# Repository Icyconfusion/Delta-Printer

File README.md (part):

# Delta Printer
An STM32 based delta style 3D printer running Marlin firmware. The printer features a custom PCB motherboard, LCD, and 220mm diameter x roughly 200mm build volume. I designed this project to expand on my understanding of 3D printer hardware and mechanics through non-standard motion.

**Note to reviewer:** My JLCPCB/MC screenshot is inclusive of tax and cheapest shipping option, it went into my "orders" tab despite not being paid for, but that is the total price, and the checkout page. Thank you:)

## Assembly
The key assembly ofthe printer is a triangular prism made of 2020 T slot aluminium profiles. Using 3d printed brackets, shorter T slots of lengths 340mm for the top and 290 for the bottom are arranged into triangles. 500mm T slot join these triangles. Two profiles are used for each tower to increase stiffness. The bottom bracket extends the height of the printer without needing extra T slot. Brackets are mounted using T nuts.

400mm MGN12H linear rails are mounted to the inside profile of each tower using M3x8 screws.

To mount the NEMA17 stepper motors, the motors are screwed into the mount bracket, which attaches to the inside of the two bottom triangles.

Bottom covers are added and the PCB is placed in the groove in the centre.

Idle pulleys are mounted to the top bracket with an M5 screw. The carriages are assembled with the ball joints screwed onto the carriage. M3 screws are threaded into the heat inserts and the GT2 belt is mounted. The carbon tube has an M3 stud glue into each end, which is threaded into the ball joint on each end.

### Effector Assembly
To assemble the effector, first mount the NEMA 17 stepper and filament gear.

Then mount the CR6-SE hotend into the heat inserts.

4010 fans mount on the back and side where they are ducted to the nozzle/part.

The extruder arm provides tension to the filament gear to ensure accurate and reliable extrusion of filament. The arm is spring loaded to push an 11x5x5 bearing, squeezing the filament against the drive gear. The arm pivots around the top left M3 NEMA 17 mounting screw. An M5 screw above this is threaded into the effector knob, and a spring in this spot provides tension. Finally, the ball joints are attached, and can be connected to the arms on the carriages.

To start closing the base compartment and installing the bed, the LCD must be installed. The LCD is screwed through the back into heat inserts in the LCD module printed part. This module is then mounted onto LCD base covers using heat inserts. This is then mounted onto the base using T nuts.

Base covers are mounted onto one of the other sides.

The third side holds the PSU. The PSU is held in its compartment, which is mounted to the frame in place. A base cover is mounted next to it. There is a hole in the base cover next to it for power cables to run from to PSU to the wall outlet.

Now the bed can be installed. To do this, printed bed supports are installed on the base. The bed then screws into these. If needed, depending on exact specifications of the bed, the holes to mount the bed can be made larger by printing or drilling.

To mount limit switches, the switches are screwed into heat inserts in the bracket, then mounted to the bottom of the towers. After this the printer is assembled.

## Electronics
The printer features a 2 layer PCB motherboard I designed around an STM32F407VGT6. TMC2209 drivers are used to control stepper motors, and subsequently motion. The board utilises mostly SMD components to minimise space and layer requirements. Power is brought onto the board using 7.62mm pitch screw terminals, which connect to the 24V 600w PSU. A buck converter and linear regulator convert this down to 5V and 3.3V logic levels. 5V is used only for the buck converter and the EXP1 header for the LCD. The LCD used it a BTT Mini 12864 V2.0, which interfaces with the PCB via EXP1 and EXP2 headers. The LCD also has an encoder, button and SD card reader. The heaters (hotend and bed if required in future) are controlled through TO-252-3 AOD4184 MOSFETs. Lower power mosfets, SOT-23 AO3400 MOSFETs, are used to control the 24V fans. There is a USB-C receptacle for firmware flashing, and an SWD header if needed. Most resistors and capacitors are size 0805, though there are exceptionswhere required. Because I am using the STM32, no external flash is required, as it is onboard.

Driver hierarchical sheet:

MOSFET hierarchical sheet:

Power:

EXP1 and EXP2:

The PCB is organised with drivers up the top. Power on the left edge, with the buck converter, regulator, power input terminal and fuse. MOSFETs are on the bottom, heaters on the right hand side. On the right edge, there is the USB-C receptacle, thermistors, endstops and LCD headers. The STM32 is situated in the center.

## Firmware
The firmware used is Marlin firmware. The firmware has been configured to match a delta printer with delta kinematics. Additionally, it has been configured for my custom motherboard by creating a unique pin mapping for the printer. The config and pin map files are in the firmware folder of the repo, along with the complete marlin .zip build folder.

## BOM
### Printed Parts

|Part| Quantity| Image|
|---|---|---|
|Bottom bracket | 3 |  |
|Top bracket | 3 |  |
|Bottom cover | 3 |  |
|Bed support | 3 |  |
|Motor mount | 3 |  |
|Carriage | 3 |  |
|PSU compartment | 3 |  |
|Base cover LCD | 2 |  |
|Base cover | 2 |  |
|Base cover PSU | 1 |  |
|LCD front cover | 1 |  |
|Extruder | 1 |  |
|Drive arm | 1 |  |
|Limit switch bracket | 3 |  |

### Parts already owned
| Part | Quantity | Description |
|--|--|--|
|T slot | 6 | 500mm 2020 T slot profiles |
|Linear rail | 3 | MGN12H 400mm linear rail and carriage |
|Motor | 4 | NEMA 17 stepper motor |
| Hotend | 1 | CR6 SE hotend |
| Fan | 2 | 4010 24v blower fan |
| GT2 bearing | 3 | 5mm bore gt2 idler bearing |
| GT2 gear | 3 | GT2 20T gear |
|LCD | 1 | BTT mini 12864 V2.0 LCD |
| Limit switch | 3 | Standard limit switch |
| T nut | - | M5 and M3 T nuts |
| PSU | 1 | 24V 600w PSU |

### Purchased parts
|Product            |Quantity|Description                                                                                                                  |Total cost (USD)|Supplier  |Link                                                                                                                                                                                                                                                                                                                                                                                                                                                                                                                                                                                                                                                                                                                                                                                                                        |
|-------------------|--------|-----------------------------------------------------------------------------------------------------------------------------|----------------|----------|----------------------------------------------------------------------------------------------------------------------------------------------------------------------------------------------------------------------------------------------------------------------------------------------------------------------------------------------------------------------------------------------------------------------------------------------------------------------------------------------------------------------------------------------------------------------------------------------------------------------------------------------------------------------------------------------------------------------------------------------------------------------------------------------------------------------------|
|100nF Capacitors   |26      |100nF 0805 ceramic capacitors for PCB                                                                                        |2.31            |Aliexpress|https://www.aliexpress.com/item/1005011894977575.html?spm=a2g0o.productlist.main.41.69b475e66t3VJX&algo_pvid=395ae593-2082-45a5-ad42-2ee72ec24400&algo_exp_id=395ae593-2082-45a5-ad42-2ee72ec24400-38&pdp_ext_f=%7B%22order%22%3A%2264%22%2C%22eval%22%3A%221%22%2C%22fromPage%22%3A%22search%22%7D&pdp_npi=6%40dis%21AUD%210.98%210.74%21%21%210.69%210.52%21%402101e2b017803787116784136eb256%2112000056926137114%21sea%21AU%210%21ABX%211%210%21n_tag%3A-29910%3Bd%3A6fbdfe4b%3Bm03_new_user%3A-29895&curPageLogUid=lO0BHaX0NqCM&utparam-url=scene%3Asearch%7Cquery_from%3A%7Cx_object_id%3A1005011894977575%7C_p_origin_prod%3A                                                                                                                                                                                         |
|100uF - Low ESR Cap|6       |50V 100uF Low ESR caps in 6.3x7.7 package. Used for Vm on TMC2209                                                            |3.69            |Aliexpress|https://www.aliexpress.com/item/1005006846973435.html                                                                                                                                                                                                                                                                                                                                                                                                                                                                                                                                                                                                                                                                                                                                                                       |
|2.2uF cap          |6       |0805 2.2uF 50V ceramic capacitors                                                                                            |2.2             |Aliexpress|https://www.aliexpress.com/item/1005007293718666.html?spm=a2g0o.productlist.main.8.67be145epeTiPJ&algo_pvid=53e6a399-9eba-48a6-b5d2-d96bd9cce18e&aem_p4p_detail=20260601225849174814213877420004833943&algo_exp_id=53e6a399-9eba-48a6-b5d2-d96bd9cce18e-7&pdp_ext_f=%7B%22order%22%3A%221222%22%2C%22spu_best_type%22%3A%22price%22%2C%22eval%22%3A%221%22%2C%22fromPage%22%3A%22search%22%7D&pdp_npi=6%40dis%21AUD%212.85%212.85%21%21%2113.59%2113.59%21%402103128917803799289523918ea094%2112000040093563143%21sea%21AU%210%21ABX%211%210%21n_tag%3A-29910%3Bd%3A6fbdfe4b%3Bm03_new_user%3A-29895&curPageLogUid=OS4dkcks5GAl&utparam-url=scene%3Asearch%7Cquery_from%3A%7Cx_object_id%3A1005007293718666%7C_p_origin_prod%3A&search_p4p_id=20260601225849174814213877420004833943_2                                      |
|22nF cap           |4       |0805 22nF 50V ca-                                                                                                            |2.2             |Aliexpress|https://www.aliexpress.com/item/1005011894977575.html?spm=a2g0o.productlist.main.41.69b475e66t3VJX&algo_pvid=395ae593-2082-45a5-ad42-2ee72ec24400&algo_exp_id=395ae593-2082-45a5-ad42-2ee72ec24400-38&pdp_ext_f=%7B%22order%22%3A%2264%22%2C%22eval%22%3A%221%22%2C%22fromPage%22%3A%22search%22%7D&pdp_npi=6%40dis%21AUD%210.98%210.74%21%21%210.69%210.52%21%402101e2b017803787116784136eb256%2112000056926137114%21sea%21AU%210%21ABX%211%210%21n_tag%3A-29910%3Bd%3A6fbdfe4b%3Bm03_new_user%3A-29895&curPageLogUid=lO0BHaX0NqCM&utparam-url=scene%3Asearch%7Cquery_from%3A%7Cx_object_id%3A1005011894977575%7C_p_origin_prod%3A                                                                                                                                                                                         |
|1uF cap            |4       |0805 1uF 50V capacitor                                                                                                       |2.04            |Aliexpress|https://www.aliexpress.com/item/1005007293718666.html?spm=a2g0o.productlist.main.8.67be145epeTiPJ&algo_pvid=53e6a399-9eba-48a6-b5d2-d96bd9cce18e&aem_p4p_detail=20260601225849174814213877420004833943&algo_exp_id=53e6a399-9eba-48a6-b5d2-d96bd9cce18e-7&pdp_ext_f=%7B%22order%22%3A%221222%22%2C%22spu_best_type%22%3A%22price%22%2C%22eval%22%3A%221%22%2C%22fromPage%22%3A%22search%22%7D&pdp_npi=6%40dis%21AUD%212.85%212.85%21%21%2113.59%2113.59%21%402103128917803799289523918ea094%2112000040093563143%21sea%21AU%210%21ABX%211%210%21n_tag%3A-29910%3Bd%3A6fbdfe4b%3Bm03_new_user%3A-29895&curPageLogUid=OS4dkcks5GAl&utparam-url=scene%3Asearch%7Cquery_from%3A%7Cx_object_id%3A1005007293718666%7C_p_origin_prod%3A&search_p4p_id=20260601225849174814213877420004833943_2                                      |
|18pF cap           |2       |0805 18pF cap for crystal                                                                                                    |2.52            |Aliexpress|https://www.aliexpress.com/item/1005002958706092.html?spm=a2g0o.productlist.main.1.3511QjeLQjeLPI&algo_pvid=3a26b9ba-d000-4d83-9a75-3d450696f550&algo_exp_id=3a26b9ba-d000-4d83-9a75-3d450696f550-0&pdp_ext_f=%7B%22order%22%3A%22135%22%2C%22eval%22%3A%221%22%2C%22fromPage%22%3A%22search%22%7D&pdp_npi=6%40dis%21AUD%211.79%211.79%21%21%211.26%211.26%21%4021030a4b17807228650825953eb029%2112000022968072311%21sea%21AU%217099856219%21ABX%211%210%21n_tag%3A-29910%3Bd%3A6fbdfe4b%3Bm03_new_user%3A-29895&curPageLogUid=HO0lalvIulA4&utparam-url=scene%3Asearch%7Cquery_from%3A%7Cx_object_id%3A1005002958706092%7C_p_origin_prod%3A                                                                                                                                                                                 |
|22uF cap           |4       |0805 22uF 50V capacitor                                                                                                      |2.86            |Aliexpress|https://www.aliexpress.com/item/1005007293718666.html?spm=a2g0o.productlist.main.8.67be145epeTiPJ&algo_pvid=53e6a399-9eba-48a6-b5d2-d96bd9cce18e&aem_p4p_detail=20260601225849174814213877420004833943&algo_exp_id=53e6a399-9eba-48a6-b5d2-d96bd9cce18e-7&pdp_ext_f=%7B%22order%22%3A%221222%22%2C%22spu_best_type%22%3A%22price%22%2C%22eval%22%3A%221%22%2C%22fromPage%22%3A%22search%22%7D&pdp_npi=6%40dis%21AUD%212.85%212.85%21%21%2113.59%2113.59%21%402103128917803799289523918ea094%2112000040093563143%21sea%21AU%210%21ABX%211%210%21n_tag%3A-29910%3Bd%3A6fbdfe4b%3Bm03_new_user%3A-29895&curPageLogUid=OS4dkcks5GAl&utparam-url=scene%3Asearch%7Cquery_from%3A%7Cx_object_id%3A1005007293718666%7C_p_origin_prod%3A&search_p4p_id=20260601225849174814213877420004833943_2                                      |
|10uF cap           |6       |0805 10uF cap                                                                                                                |2.54            |Aliexpress|https://www.aliexpress.com/item/1005007293718666.html?spm=a2g0o.productlist.main.8.67be145epeTiPJ&algo_pvid=53e6a399-9eba-48a6-b5d2-d96bd9cce18e&aem_p4p_detail=20260601225849174814213877420004833943&algo_exp_id=53e6a399-9eba-48a6-b5d2-d96bd9cce18e-7&pdp_ext_f=%7B%22order%22%3A%221222%22%2C%22spu_best_type%22%3A%22price%22%2C%22eval%22%3A%221%22%2C%22fromPage%22%3A%22search%22%7D&pdp_npi=6%40dis%21AUD%212.85%212.85%21%21%2113.59%2113.59%21%402103128917803799289523918ea094%2112000040093563143%21sea%21AU%210%21ABX%211%210%21n_tag%3A-29910%3Bd%3A6fbdfe4b%3Bm03_new_user%3A-29895&curPageLogUid=OS4dkcks5GAl&utparam-url=scene%3Asearch%7Cquery_from%3A%7Cx_object_id%3A1005007293718666%7C_p_origin_prod%3A&search_p4p_id=20260601225849174814213877420004833943_2                                      |
|220pF cap          |1       |0805 220pF 50V cap                                                                                                           |4.04            |Aliexpress|https://www.aliexpress.com/item/1005011884524334.html?spm=a2g0o.productlist.main.8.50ab6ab5yWojEX&algo_pvid=5edf1c78-ef25-4421-bfb1-3e1d6e4784bc&algo_exp_id=5edf1c78-ef25-4421-bfb1-3e1d6e4784bc-7&pdp_ext_f=%7B%22order%22%3A%2235%22%2C%22eval%22%3A%221%22%2C%22fromPage%22%3A%22search%22%7D&pdp_npi=6%40dis%21AUD%213.81%211.79%21%21%2118.11%218.51%21%40210328d417806369446965838ef751%2112000056880413140%21sea%21AU%210%21ABX%211%210%21n_tag%3A-29910%3Bd%3A6fbdfe4b%3Bm03_new_user%3A-29895&curPageLogUid=1xTiDLuHV5Su&utparam-url=scene%3Asearch%7Cquery_from%3A%7Cx_object_id%3A1005011884524334%7C_p_origin_prod%3A                                                                                                                                                                                          |
|SS34 diode         |1       |SS34 SMA Schottky diode                                                                                                      |2.89            |Aliexpress|https://www.aliexpress.com/item/1005003929814084.html?spm=a2g0o.productlist.main.1.7ba564e91Bl9Po&algo_pvid=39ff2f7f-65b5-4324-9e76-e1229462bde4&algo_exp_id=39ff2f7f-65b5-4324-9e76-e1229462bde4-0&pdp_ext_f=%7B%22order%22%3A%22312%22%2C%22eval%22%3A%221%22%2C%22fromPage%22%3A%22search%22%7D&pdp_npi=6%40dis%21AUD%213.94%211.41%21%21%212.76%210.98%21%402101ef5e17806371422707336ed5cd%2112000027492300397%21sea%21AU%210%21ABX%211%210%21n_tag%3A-29910%3Bd%3A6fbdfe4b%3Bm03_new_user%3A-29895%3BpisId%3A5000000204867275&curPageLogUid=NnPur3r1YfyF&utparam-url=scene%3Asearch%7Cquery_from%3A%7Cx_object_id%3A1005003929814084%7C_p_origin_prod%3A                                                                                                                                                               |
|Ferrite bead       |1       |0805 600R 100mhz ferrite bead                                                                                                |3.93            |Aliexpress|https://www.aliexpress.com/item/1005003127666910.html?spm=a2g0o.productlist.main.37.ba11ISfCISfCeO&algo_pvid=b19fe644-ee9e-45ce-8c38-43ce983eb4d3&algo_exp_id=b19fe644-ee9e-45ce-8c38-43ce983eb4d3-34&pdp_ext_f=%7B%22order%22%3A%2225%22%2C%22eval%22%3A%221%22%2C%22fromPage%22%3A%22search%22%7D&pdp_npi=6%40dis%21AUD%215.52%214.72%21%21%213.87%213.31%21%40210337c117807205436898267e16f1%2112000024246365910%21sea%21AU%217099856219%21ABX%211%210%21n_tag%3A-29910%3Bd%3A6fbdfe4b%3Bm03_new_user%3A-29895&curPageLogUid=ES5AkXMpY2mV&utparam-url=scene%3Asearch%7Cquery_from%3A%7Cx_object_id%3A1005003127666910%7C_p_origin_prod%3A                                                                                                                                                                                |
|IDC header         |2       |2x5 pin 2.54mm IDC header for EXP1/2                                                                                         |4.77            |Aliexpress|https://www.aliexpress.com/item/32658384492.html?spm=a2g0o.productlist.main.1.219e2670Eo0Se8&algo_pvid=fe8eff41-56a5-4592-8ccd-295c5888be36&algo_exp_id=fe8eff41-56a5-4592-8ccd-295c5888be36-0&pdp_ext_f=%7B%22order%22%3A%22191%22%2C%22eval%22%3A%221%22%2C%22fromPage%22%3A%22search%22%7D&pdp_npi=6%40dis%21AUD%213.22%211.15%21%21%212.26%210.81%21%402101eecd17806372074926845e0b1c%2159817550672%21sea%21AU%210%21ABX%211%210%21n_tag%3A-29910%3Bd%3A6fbdfe4b%3Bm03_new_user%3A-29895&curPageLogUid=g4IB6NhYXd4C&utparam-url=scene%3Asearch%7Cquery_from%3A%7Cx_object_id%3A32658384492%7C_p_origin_prod%3A                                                                                                                                                                                                          |
|JST-XH header      |7       |JST-XH 2.54mm header for conencting heaters and fans                                                                         |1.83            |Aliexpress|https://www.aliexpress.com/item/1005004985397880.html?spm=a2g0o.productlist.main.23.40e65899Of5PUE&algo_pvid=1977cbec-ffa5-4de8-831c-9440196d8bf1&algo_exp_id=1977cbec-ffa5-4de8-831c-9440196d8bf1-22&pdp_ext_f=%7B%22order%22%3A%222875%22%2C%22eval%22%3A%221%22%2C%22fromPage%22%3A%22search%22%7D&pdp_npi=6%40dis%21AUD%211.97%211.41%21%21%211.38%210.99%21%402101e2b417806373261363795eedd2%2112000031243962104%21sea%21AU%210%21ABX%211%210%21n_tag%3A-29910%3Bd%3A6fbdfe4b%3Bm03_new_user%3A-29895%3BpisId%3A5000000204867275&curPageLogUid=7n7ud5jLy3vZ&utparam-url=scene%3Asearch%7Cquery_from%3A%7Cx_object_id%3A1005004985397880%7C_p_origin_prod%3A                                                                                                                                                            |
|10uH inductor      |1       |6x6x3 10uH inductor                                                                                                          |3.5             |Aliexpress|https://www.aliexpress.com/item/1005006817003873.html?spm=a2g0o.productlist.main.6.307049c0TMTVHT&algo_pvid=e79df2b3-a062-49aa-af8c-c6f5cb47ec49&algo_exp_id=e79df2b3-a062-49aa-af8c-c6f5cb47ec49-5&pdp_ext_f=%7B%22order%22%3A%22163%22%2C%22eval%22%3A%221%22%2C%22fromPage%22%3A%22search%22%7D&pdp_npi=6%40dis%21AUD%214.18%213.83%21%21%2119.87%2118.21%21%402103274e17807207366446547eda14%2112000038400661794%21sea%21AU%217099856219%21ABX%211%210%21n_tag%3A-29910%3Bd%3A6fbdfe4b%3Bm03_new_user%3A-29895&curPageLogUid=Uw0smIdCVuNn&utparam-url=scene%3Asearch%7Cquery_from%3A%7Cx_object_id%3A1005006817003873%7C_p_origin_prod%3A                                                                                                                                                                               |
|MOSFET             |2       |TO252-3 AOD4184 SMD MOSFET for heaters                                                                                       |3.7             |Aliexpress|https://www.aliexpress.com/item/1005006044488568.html?spm=a2g0o.productlist.main.11.4d4c3b5bR8SclD&algo_pvid=a61fbf26-45db-4a52-9034-cc3dcb697579&algo_exp_id=a61fbf26-45db-4a52-9034-cc3dcb697579-10&pdp_ext_f=%7B%22order%22%3A%2295%22%2C%22eval%22%3A%221%22%2C%22fromPage%22%3A%22search%22%7D&pdp_npi=6%40dis%21AUD%215.19%215.19%21%21%213.64%213.64%21%402101d6fe17807216896738122e0f1a%2112000035465188545%21sea%21AU%217099856219%21ABX%211%210%21n_tag%3A-29910%3Bd%3A6fbdfe4b%3Bm03_new_user%3A-29895&curPageLogUid=S5OfV9YlN4WJ&utparam-url=scene%3Asearch%7Cquery_from%3A%7Cx_object_id%3A1005006044488568%7C_p_origin_prod%3A                                                                                                                                                                                |
|Fan MOSFET         |3       |SOT-23 AO3400 SMD MOSFET                                                                                                     |1.87            |Aliexpress|https://www.aliexpress.com/item/1005006286601118.html?spm=a2g0o.productlist.main.9.4ce42ca8iM3y0D&algo_pvid=319f8fc6-8206-46b1-9744-9ac8f71bc98b&algo_exp_id=319f8fc6-8206-46b1-9744-9ac8f71bc98b-8&pdp_ext_f=%7B%22order%22%3A%22371%22%2C%22spu_best_type%22%3A%22price%22%2C%22eval%22%3A%221%22%2C%22fromPage%22%3A%22search%22%7D&pdp_npi=6%40dis%21AUD%212.63%211.41%21%21%2112.49%216.69%21%402101df0e17807218619116715e442e%2112000036629120259%21sea%21AU%217099856219%21ABX%211%210%21n_tag%3A-29910%3Bd%3A6fbdfe4b%3Bm03_new_user%3A-29895%3BpisId%3A5000000204867275&curPageLogUid=dHrfVQrllnN6&utparam-url=scene%3Asearch%7Cquery_from%3A%7Cx_object_id%3A1005006286601118%7C_p_origin_prod%3A                                                                                                                 |
|Resistor 0.5W      |8       |1206 0.5W 0.15 ohm sense resistor for TMC 2209                                                                               |1.62            |Aliexpress|https://www.aliexpress.com/item/1005005905538731.html?spm=a2g0o.productlist.main.22.23a1qQ8UqQ8UMb&algo_pvid=a82ca72a-9188-440a-b602-617bfa6c08b9&algo_exp_id=a82ca72a-9188-440a-b602-617bfa6c08b9-21&pdp_ext_f=%7B%22order%22%3A%2295%22%2C%22eval%22%3A%221%22%2C%22fromPage%22%3A%22search%22%7D&pdp_npi=6%40dis%21AUD%212.28%212.28%21%21%211.60%211.60%21%40210319b717807247218277738eef46%2112000034790583111%21sea%21AU%217099856219%21ABX%211%210%21n_tag%3A-29910%3Bd%3A6fbdfe4b%3Bm03_new_user%3A-29895&curPageLogUid=Pfo42AofQ8rk&utparam-url=scene%3Asearch%7Cquery_from%3A%7Cx_object_id%3A1005005905538731%7C_p_origin_prod%3A                                                                                                                                                                                |
|1K resistor        |5       |0805 1k ohm resistor                                                                                                         |2.48            |Aliexpress|https://www.aliexpress.com/item/32936483115.html?spm=a2g0o.productlist.main.17.1568609eeUmkpk&algo_pvid=3f253524-d59c-408c-95f4-7682587921c2&algo_exp_id=3f253524-d59c-408c-95f4-7682587921c2-16&pdp_ext_f=%7B%22order%22%3A%22226%22%2C%22eval%22%3A%221%22%2C%22fromPage%22%3A%22search%22%7D&pdp_npi=6%40dis%21AUD%213.38%213.38%21%21%212.37%212.37%21%402101df0e17806374475111340ea6b0%2166160253242%21sea%21AU%210%21ABX%211%210%21n_tag%3A-29910%3Bd%3A6fbdfe4b%3Bm03_new_user%3A-29895&curPageLogUid=dNfs5t7vpWyj&utparam-url=scene%3Asearch%7Cquery_from%3A%7Cx_object_id%3A32936483115%7C_p_origin_prod%3A                                                                                                                                                                                                        |
|10k resistor       |12      |0805 10k resistor                                                                                                            |2.53            |Aliexpress|https://www.aliexpress.com/item/32936483115.html?spm=a2g0o.productlist.main.17.1568609eeUmkpk&algo_pvid=3f253524-d59c-408c-95f4-7682587921c2&algo_exp_id=3f253524-d59c-408c-95f4-7682587921c2-16&pdp_ext_f=%7B%22order%22%3A%22226%22%2C%22eval%22%3A%221%22%2C%22fromPage%22%3A%22search%22%7D&pdp_npi=6%40dis%21AUD%213.38%213.38%21%21%212.37%212.37%21%402101df0e17806374475111340ea6b0%2166160253242%21sea%21AU%210%21ABX%211%210%21n_tag%3A-29910%3Bd%3A6fbdfe4b%3Bm03_new_user%3A-29895&curPageLogUid=dNfs5t7vpWyj&utparam-url=scene%3Asearch%7Cquery_from%3A%7Cx_object_id%3A32936483115%7C_p_origin_prod%3A                                                                                                                                                                                                        |
|100 resistor       |6       |100 ohm 0805 resistor                                                                                                        |2.44            |Aliexpress|https://www.aliexpress.com/item/32936483115.html?spm=a2g0o.productlist.main.17.1568609eeUmkpk&algo_pvid=3f253524-d59c-408c-95f4-7682587921c2&algo_exp_id=3f253524-d59c-408c-95f4-7682587921c2-16&pdp_ext_f=%7B%22order%22%3A%22226%22%2C%22eval%22%3A%221%22%2C%22fromPage%22%3A%22search%22%7D&pdp_npi=6%40dis%21AUD%213.38%213.38%21%21%212.37%212.37%21%402101df0e17806374475111340ea6b0%2166160253242%21sea%21AU%210%21ABX%211%210%21n_tag%3A-29910%3Bd%3A6fbdfe4b%3Bm03_new_user%3A-29895&curPageLogUid=dNfs5t7vpWyj&utparam-url=scene%3Asearch%7Cquery_from%3A%7Cx_object_id%3A32936483115%7C_p_origin_prod%3A                                                                                                                                                                                                        |
|5.1K resistor      |2       |0805 5.1k resistor                                                                                                           |2.48            |Aliexpress|https://www.aliexpress.com/item/32936483115.html?spm=a2g0o.productlist.main.17.1568609eeUmkpk&algo_pvid=3f253524-d59c-408c-95f4-7682587921c2&algo_exp_id=3f253524-d59c-408c-95f4-7682587921c2-16&pdp_ext_f=%7B%22order%22%3A%22226%22%2C%22eval%22%3A%221%22%2C%22fromPage%22%3A%22search%22%7D&pdp_npi=6%40dis%21AUD%213.38%213.38%21%21%212.37%212.37%21%402101df0e17806374475111340ea6b0%2166160253242%21sea%21AU%210%21ABX%211%210%21n_tag%3A-29910%3Bd%3A6fbdfe4b%3Bm03_new_user%3A-29895&curPageLogUid=dNfs5t7vpWyj&utparam-url=scene%3Asearch%7Cquery_from%3A%7Cx_object_id%3A32936483115%7C_p_origin_prod%3A                                                                                                                                                                                                        |
|33 resistor        |2       |0805 33 ohm resistor                                                                                                         |2.44            |Aliexpress|https://www.aliexpress.com/item/32936483115.html?spm=a2g0o.productlist.main.17.1568609eeUmkpk&algo_pvid=3f253524-d59c-408c-95f4-7682587921c2&algo_exp_id=3f253524-d59c-408c-95f4-7682587921c2-16&pdp_ext_f=%7B%22order%22%3A%22226%22%2C%22eval%22%3A%221%22%2C%22fromPage%22%3A%22search%22%7D&pdp_npi=6%40dis%21AUD%213.38%213.38%21%21%212.37%212.37%21%402101df0e17806374475111340ea6b0%2166160253242%21sea%21AU%210%21ABX%211%210%21n_tag%3A-29910%3Bd%3A6fbdfe4b%3Bm03_new_user%3A-29895&curPageLogUid=dNfs5t7vpWyj&utparam-url=scene%3Asearch%7Cquery_from%3A%7Cx_object_id%3A32936483115%7C_p_origin_prod%3A                                                                                                                                                                                                        |
|52.3K resistor     |1       |0805 52.3k resistor                                                                                                          |1.8             |Aliexpress|https://www.aliexpress.com/item/1005005184354247.html?spm=a2g0o.productlist.main.1.12dfnIy4nIy4Db&algo_pvid=04236b54-eea0-456f-b46d-5a8e50e54835&algo_exp_id=04236b54-eea0-456f-b46d-5a8e50e54835-0&pdp_ext_f=%7B%22order%22%3A%2275%22%2C%22spu_best_type%22%3A%22price%22%2C%22eval%22%3A%221%22%2C%22fromPage%22%3A%22search%22%7D&pdp_npi=6%40dis%21AUD%212.52%212.52%21%21%2111.99%2111.99%21%402101d6ff17807224801268541e7688%2112000032017603960%21sea%21AU%217099856219%21ABX%211%210%21n_tag%3A-29910%3Bd%3A6fbdfe4b%3Bm03_new_user%3A-29895&curPageLogUid=rQRCWdSXORAa&utparam-url=scene%3Asearch%7Cquery_from%3A%7Cx_object_id%3A1005005184354247%7C_p_origin_prod%3A                                                                                                                                            |
|100k resistor      |1       |0805 100k resistor                                                                                                           |3.04            |Aliexpress|https://www.aliexpress.com/item/1005007183002569.html?spm=a2g0o.productlist.main.1.23aaF519F5192b&algo_pvid=0c0e1b7a-10d1-428c-a6a4-4f6f3e54d974&algo_exp_id=0c0e1b7a-10d1-428c-a6a4-4f6f3e54d974-0&pdp_ext_f=%7B%22order%22%3A%2226%22%2C%22eval%22%3A%221%22%2C%22fromPage%22%3A%22search%22%7D&pdp_npi=6%40dis%21AUD%214.00%211.41%21%21%2118.99%216.68%21%402101e2b217807245707611530eb4e2%2112000039726416947%21sea%21AU%217099856219%21ABX%211%210%21n_tag%3A-29910%3Bd%3A6fbdfe4b%3Bm03_new_user%3A-29895%3BpisId%3A5000000204867275&curPageLogUid=CMCONd03B1Mp&utparam-url=scene%3Asearch%7Cquery_from%3A%7Cx_object_id%3A1005007183002569%7C_p_origin_prod%3A                                                                                                                                                      |
|24.9K resistor     |1       |0805 24.9k resistor                                                                                                          |1.72            |Aliexpress|https://www.aliexpress.com/item/1005005184354288.html?spm=a2g0o.productlist.main.1.2f24B0W0B0W0a9&algo_pvid=3ed91e8e-ee43-4506-bb40-daf68fe7f93e&algo_exp_id=3ed91e8e-ee43-4506-bb40-daf68fe7f93e-0&pdp_ext_f=%7B%22order%22%3A%2226%22%2C%22eval%22%3A%221%22%2C%22fromPage%22%3A%22search%22%7D&pdp_npi=6%40dis%21AUD%212.40%212.40%21%21%2111.41%2111.41%21%402101f54117807224441317846e69eb%2112000032017704493%21sea%21AU%217099856219%21ABX%211%210%21n_tag%3A-29910%3Bd%3A6fbdfe4b%3Bm03_new_user%3A-29895&curPageLogUid=G58tsGOWqItU&utparam-url=scene%3Asearch%7Cquery_from%3A%7Cx_object_id%3A1005005184354288%7C_p_origin_prod%3A                                                                                                                                                                                |
|68.1K resistor     |1       |0805 68.1k resistor                                                                                                          |1.72            |Aliexpress|https://www.aliexpress.com/item/1005005187548543.html?spm=a2g0o.productlist.main.13.4056LFJ1LFJ16D&algo_pvid=f24fb5dd-aa8d-4876-b9c8-f9de646a9ed7&algo_exp_id=f24fb5dd-aa8d-4876-b9c8-f9de646a9ed7-12&pdp_ext_f=%7B%22order%22%3A%2221%22%2C%22eval%22%3A%221%22%2C%22fromPage%22%3A%22search%22%7D&pdp_npi=6%40dis%21AUD%212.42%212.42%21%21%2111.49%2111.49%21%402101e8f317807225468668995e5f76%2112000032029087535%21sea%21AU%217099856219%21ABX%211%210%21n_tag%3A-29910%3Bd%3A6fbdfe4b%3Bm03_new_user%3A-29895&curPageLogUid=MXuPuWllAnmZ&utparam-url=scene%3Asearch%7Cquery_from%3A%7Cx_object_id%3A1005005187548543%7C_p_origin_prod%3A                                                                                                                                                                              |
|22 resistor        |2       |0805 22 ohm resistor                                                                                                         |2.59            |Aliexpress|https://www.aliexpress.com/item/32936483115.html?spm=a2g0o.productlist.main.17.1568609eeUmkpk&algo_pvid=3f253524-d59c-408c-95f4-7682587921c2&algo_exp_id=3f253524-d59c-408c-95f4-7682587921c2-16&pdp_ext_f=%7B%22order%22%3A%22226%22%2C%22eval%22%3A%221%22%2C%22fromPage%22%3A%22search%22%7D&pdp_npi=6%40dis%21AUD%213.38%213.38%21%21%212.37%212.37%21%402101df0e17806374475111340ea6b0%2166160253242%21sea%21AU%210%21ABX%211%210%21n_tag%3A-29910%3Bd%3A6fbdfe4b%3Bm03_new_user%3A-29895&curPageLogUid=dNfs5t7vpWyj&utparam-url=scene%3Asearch%7Cquery_from%3A%7Cx_object_id%3A32936483115%7C_p_origin_prod%3A                                                                                                                                                                                                        |
|Pushbutton         |1       |TS-1088-AR02016 pushbutton                                                                                                   |1.09            |Aliexpress|https://www.aliexpress.com/item/1005011940516004.html?spm=a2g0o.productlist.main.1.1dc934cfNKT6pK&algo_pvid=17b3d164-d881-40d8-9241-9f836ec8db4b&algo_exp_id=17b3d164-d881-40d8-9241-9f836ec8db4b-0&pdp_ext_f=%7B%22order%22%3A%2215%22%2C%22eval%22%3A%221%22%2C%22fromPage%22%3A%22search%22%7D&pdp_npi=6%40dis%21AUD%211.53%211.41%21%21%211.07%210.99%21%402101d97817806377084755083e3403%2112000057087204873%21sea%21AU%210%21ABX%211%210%21n_tag%3A-29910%3Bd%3A6fbdfe4b%3Bm03_new_user%3A-29895%3BpisId%3A5000000204867275&curPageLogUid=CfBxlh486V12&utparam-url=scene%3Asearch%7Cquery_from%3A%7Cx_object_id%3A1005011940516004%7C_p_origin_prod%3A                                                                                                                                                                |
|STM32              |1       |STM32F407VGT6 MCU                                                                                                            |4.58            |Aliexpress|https://www.aliexpress.com/item/1005006367005179.html?spm=a2g0o.productlist.main.9.70df525dugHZ6j&algo_pvid=7f98d2dc-5be6-4900-84eb-731bfec644cb&algo_exp_id=7f98d2dc-5be6-4900-84eb-731bfec644cb-8&pdp_ext_f=%7B%22order%22%3A%22100%22%2C%22spu_best_type%22%3A%22price%22%2C%22eval%22%3A%221%22%2C%22fromPage%22%3A%22search%22%7D&pdp_npi=6%40dis%21AUD%215.69%215.69%21%21%2127.02%2127.02%21%4021030a4b17806379411333328e152f%2112000036919660259%21sea%21AU%210%21ABX%211%210%21n_tag%3A-29910%3Bd%3A6fbdfe4b%3Bm03_new_user%3A-29895&curPageLogUid=dqBBw4AoHYAD&utparam-url=scene%3Asearch%7Cquery_from%3A%7Cx_object_id%3A1005006367005179%7C_p_origin_prod%3A                                                                                                                                                    |
|TMC2209-LA         |4       |TMC 2209 stepper driver                                                                                                      |7.12            |Aliexpress|https://www.aliexpress.com/item/1005009186342077.html?spm=a2g0o.productlist.main.1.66caLyjcLyjczw&algo_pvid=8f8e6fdb-a342-40e8-baa8-5fbd1b46aa8a&algo_exp_id=8f8e6fdb-a342-40e8-baa8-5fbd1b46aa8a-0&pdp_ext_f=%7B%22order%22%3A%2233%22%2C%22eval%22%3A%221%22%2C%22fromPage%22%3A%22search%22%7D&pdp_npi=6%40dis%21AUD%215.62%215.62%21%21%213.94%213.94%21%402103123917806378749524078eb4ed%2112000048231732585%21sea%21AU%210%21ABX%211%210%21n_tag%3A-29910%3Bd%3A6fbdfe4b%3Bm03_new_user%3A-29895&curPageLogUid=HlIqvvGecP1u&utparam-url=scene%3Asearch%7Cquery_from%3A%7Cx_object_id%3A1005009186342077%7C_p_origin_prod%3A                                                                                                                                                                                           |
|MP1584-EN          |1       |Buck converter for 24V to 5V                                                                                                 |3.23            |Aliexpress|https://www.aliexpress.com/item/1005007296268441.html?spm=a2g0o.productlist.main.36.5ade3d16A6IrXa&algo_pvid=a8dc3dad-cdf6-44a5-bb8a-cabc7dbffc69&algo_exp_id=a8dc3dad-cdf6-44a5-bb8a-cabc7dbffc69-33&pdp_ext_f=%7B%22order%22%3A%2260%22%2C%22spu_best_type%22%3A%22price%22%2C%22eval%22%3A%221%22%2C%22fromPage%22%3A%22search%22%7D&pdp_npi=6%40dis%21AUD%214.53%214.53%21%21%2121.55%2121.55%21%4021030a4b17806378042748736e152f%2112000040102690817%21sea%21AU%210%21ABX%211%210%21n_tag%3A-29910%3Bd%3A6fbdfe4b%3Bm03_new_user%3A-29895&curPageLogUid=A34AWEWBjMRx&utparam-url=scene%3Asearch%7Cquery_from%3A%7Cx_object_id%3A1005007296268441%7C_p_origin_prod%3A                                                                                                                                                   |
|AP-2112K-3.3       |1       |Linear regulator for 5V to 3.3V                                                                                              |2.43            |Aliexpress|https://www.aliexpress.com/item/1005009023441155.html?spm=a2g0o.productlist.main.2.241c1e98X4V5BS&algo_pvid=21b975a3-9597-46ee-8488-f4d2a6989266&algo_exp_id=21b975a3-9597-46ee-8488-f4d2a6989266-1&pdp_ext_f=%7B%22order%22%3A%2281%22%2C%22spu_best_type%22%3A%22price%22%2C%22eval%22%3A%221%22%2C%22fromPage%22%3A%22search%22%7D&pdp_npi=6%40dis%21AUD%213.41%213.41%21%21%212.39%212.39%21%402103129017806377559721905e1d18%2112000047616340032%21sea%21AU%210%21ABX%211%210%21n_tag%3A-29910%3Bd%3A6fbdfe4b%3Bm03_new_user%3A-29895&curPageLogUid=zwSUqLx0jcxh&utparam-url=scene%3Asearch%7Cquery_from%3A%7Cx_object_id%3A1005009023441155%7C_p_origin_prod%3A                                                                                                                                                       |
|Crystal            |1       |8mhz 3225 SMD crystal, 4 pad                                                                                                 |3               |Aliexpress|https://www.aliexpress.com/item/1005005834614422.html?spm=a2g0o.productlist.main.3.7dc1447dkK6VMa&algo_pvid=4241327a-79bf-4a95-a21b-982addefa726&algo_exp_id=4241327a-79bf-4a95-a21b-982addefa726-2&pdp_ext_f=%7B%22order%22%3A%22118%22%2C%22eval%22%3A%221%22%2C%22fromPage%22%3A%22search%22%7D&pdp_npi=6%40dis%21AUD%213.22%213.22%21%21%212.26%212.26%21%40210311cc17807202394975093e5d37%2112000034516387959%21sea%21AU%217099856219%21ABX%211%210%21n_tag%3A-29910%3Bd%3A6fbdfe4b%3Bm03_new_user%3A-29895&curPageLogUid=t2KRH5g72Zws&utparam-url=scene%3Asearch%7Cquery_from%3A%7Cx_object_id%3A1005005834614422%7C_p_origin_prod%3A                                                                                                                                                                                 |
|Bed                |1       |220mm diameter kossel delta 3d print bed                                                                                     |18.8            |Aliexpress|https://www.aliexpress.com/item/33042838050.html?spm=a2g0o.productlist.0.0.70df525dugHZ6j&mp=1&pdp_npi=6%40dis%21AUD%21AUD+29.32%21AUD+26.39%21%21AUD+26.39%21%21%21%402101e80317806379429297361eb1fb%2167316263787%21ct%21AU%21-1%21%211%210%21                                                                                                                                                                                                                                                                                                                                                                                                                                                                                                                                                                            |
|Carbon tube        |2       |500mm lengths of 8x6 carbon fibre tube. Comes in packs of two, I will need two packs, and cut each rod into two 230mm lengths|14              |Aliexpress|https://www.aliexpress.com/item/1005006133534969.html?spm=a2g0o.cart.0.0.5c4838datZJxjb&mp=1&pdp_npi=6%40dis%21AUD%21AUD+12.48%21AUD+9.61%21%21AUD+9.61%21%21%21%4021030a6217807095274734870e0808%2112000035992834041%21ct%21AU%217099856219%21%213%210%21                                                                                                                                                                                                                                                                                                                                                                                                                                                                                                                                                                  |
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
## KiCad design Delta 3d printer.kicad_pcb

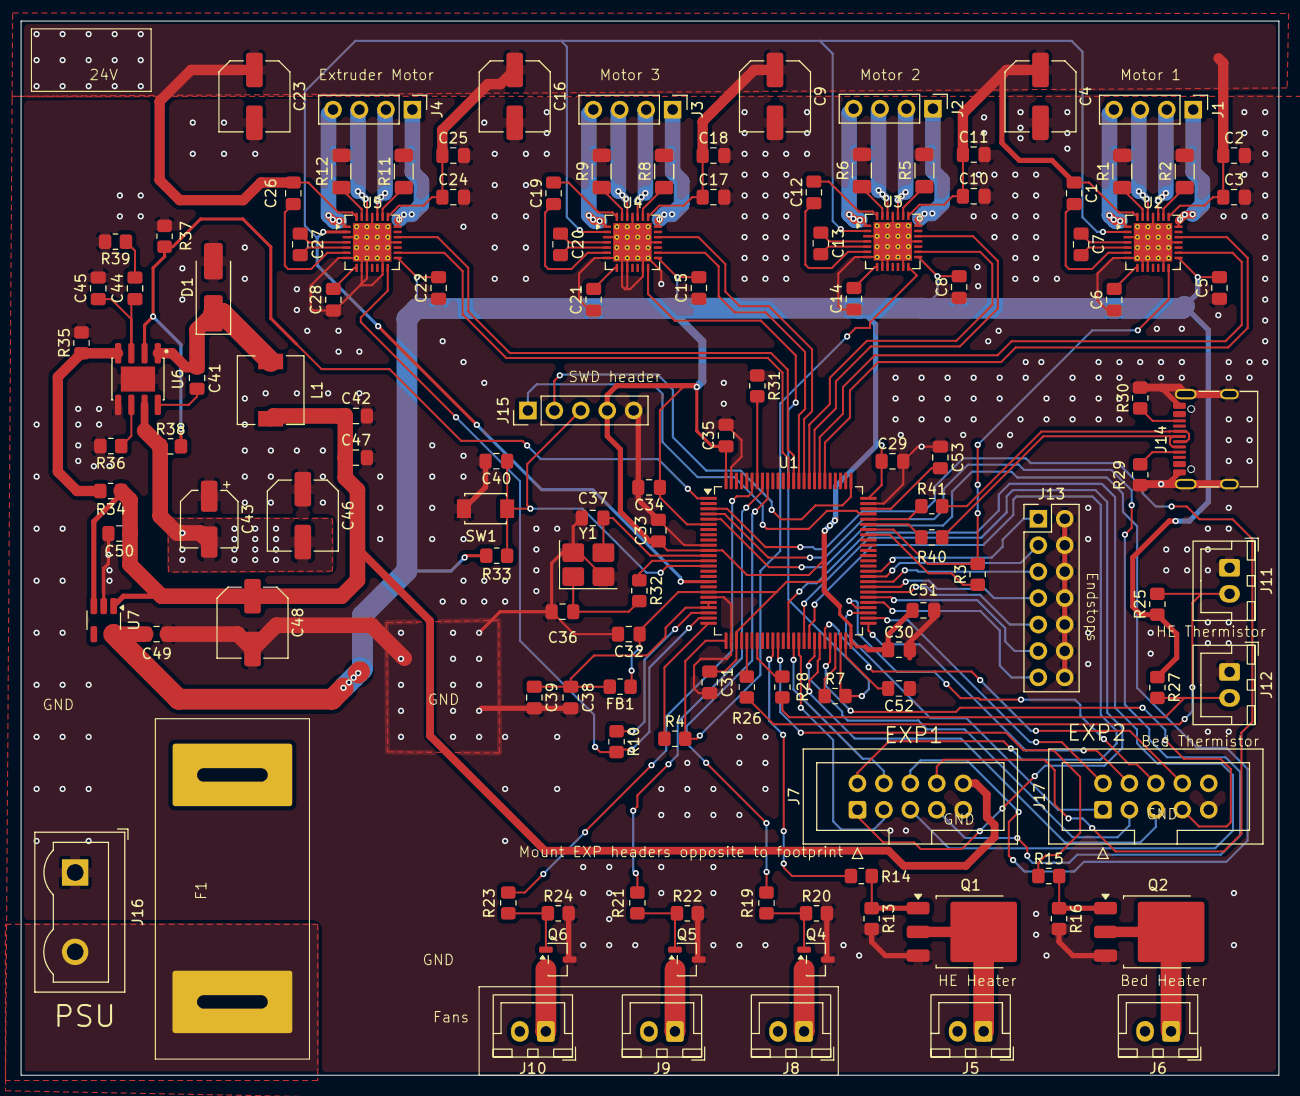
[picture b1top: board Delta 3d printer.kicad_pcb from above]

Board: 2 copper layers, 120.8 x 101.2 mm, 127 parts (0 on the bottom side), 127 nets.

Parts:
C1, C12, C19, C26: 100n 16v; C_0805_2012Metric_Pad1.18x1.45mm_HandSolder
C2, C3, C5, C8, C10, C11, C15, C17, C18, C22, C24, C25: 100n; C_0805_2012Metric_Pad1.18x1.45mm_HandSolder
C4, C9, C16, C23: 100uF - Low ESR; C_Elec_6.3x7.7
C6, C14, C21, C28: 2.2u 5v; C_0805_2012Metric_Pad1.18x1.45mm_HandSolder
C7, C13, C20, C27: 22n 50v; C_0805_2012Metric_Pad1.18x1.45mm_HandSolder
C29, C38, C49, C50: 1uF; C_0805_2012Metric_Pad1.18x1.45mm_HandSolder
C30, C31, C32, C33, C34, C35, C39, C40, C41: 100; C_0805_2012Metric_Pad1.18x1.45mm_HandSolder
C36, C37: 18pf; C_0805_2012Metric_Pad1.18x1.45mm_HandSolder
C42, C47: 22uF; C_0805_2012Metric_Pad1.18x1.45mm_HandSolder
C43: 10uf 50v; CP_Elec_5x5.4
C44: 220pF; C_0805_2012Metric_Pad1.18x1.45mm_HandSolder
C45, C51: C; C_0805_2012Metric_Pad1.18x1.45mm_HandSolder
C46: 47-100uF Electrolytic; C_Elec_6.3x7.7
C48: 100uF electrolytic; C_Elec_6.3x7.7
C52, C53: 2.2uF ceramic - low ESR; C_0805_2012Metric_Pad1.18x1.45mm_HandSolder
D1: SS34; D_SMA_Handsoldering
F1: Fuse; Fuse_Holder_KCD3_Medium
FB1: FerriteBead; R_0805_2012Metric_Pad1.20x1.40mm_HandSolder
J1, J2, J3, J4: Conn_01x04; PinHeader_1x04_P2.54mm_Vertical
J5, J6, J8, J9, J10: Screw_Terminal_01x02; JST_XH_B2B-XH-A_1x02_P2.50mm_Vertical
J7, J17: Conn_02x05_Odd_Even; IDC-Header_2x05_P2.54mm_Vertical
J11, J12: Conn_01x02; JST_XH_B2B-XH-A_1x02_P2.50mm_Vertical
J13: Conn_02x07_Odd_Even; PinHeader_2x07_P2.54mm_Vertical
J14: USB_C_Receptacle_USB2.0_16P; USB_C_Receptacle_G-Switch_GT-USB-7010ASV
J15: Conn_01x05; PinHeader_1x05_P2.54mm_Vertical
J16: Screw_Terminal_01x02; Wuerth_691311400102_P7.62mm
L1: 10uH; L_6.3x6.3_H3
Q1, Q2: Q_NMOS_GDS; TO-252-3_TabPin2
Q4, Q5, Q6: Q_NMOS_GDS; SOT-23-3
R1, R6, R9, R12: Sense B; R_1206_3216Metric_Pad1.30x1.75mm_HandSolder
R2, R5, R8, R11: 1206, 0.5w; R_1206_3216Metric_Pad1.30x1.75mm_HandSolder
R3, R4, R7, R10: 1k; R_0805_2012Metric_Pad1.20x1.40mm_HandSolder
R13, R16, R20, R22, R24, R31, R33, R35: 10k; R_0805_2012Metric_Pad1.20x1.40mm_HandSolder
R14, R15, R19, R21, R23: 100?; R_0805_2012Metric_Pad1.20x1.40mm_HandSolder
R25, R26, R27, R28, R38: R; R_0805_2012Metric_Pad1.20x1.40mm_HandSolder
R29, R30: 5.1k; R_0805_2012Metric_Pad1.20x1.40mm_HandSolder
R32: 33; R_0805_2012Metric_Pad1.20x1.40mm_HandSolder
R34: 52.3k; R_0805_2012Metric_Pad1.20x1.40mm_HandSolder
R36: 100k; R_0805_2012Metric_Pad1.20x1.40mm_HandSolder
R37: 24.9k; R_0805_2012Metric_Pad1.20x1.40mm_HandSolder
R39: 68.1k; R_0805_2012Metric_Pad1.20x1.40mm_HandSolder
R40, R41: 22; R_0805_2012Metric_Pad1.20x1.40mm_HandSolder
SW1: SW_Push; SW_TS-1088-AR02016
U1: STM32F407VGTx; LQFP-100_14x14mm_P0.5mm
U2, U3, U4, U5: TMC2209-LA; VQFN-28-1EP_5x5mm_P0.5mm_EP3.7x3.7mm_ThermalVias
U6: MP1584EN; SOIC127P600X170-9N
U7: AP2112K-3.3; SOT-23-5_HandSoldering
Y1: Crystal_GND24; Crystal_SMD_3225-4Pin_3.2x2.5mm_HandSoldering

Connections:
+3.3V: C5.2, C8.2, C15.2, C22.2, C29.1, C30.1, C31.1, C32.1, C33.1, C34.1, C35.1, C49.1, C51.2, FB1.1, J15.4, R25.1, R27.1, R33.1, U1.6 (VBAT), U1.11 (VDD), U1.19 (VDD), U1.28 (VDD), U1.50 (VDD), U1.75 (VDD), U1.100 (VDD), U2.15 (VCC_IO), U3.15 (VCC_IO), U4.15 (VCC_IO), U5.15 (VCC_IO), U7.5 (VOUT)
+5V: C42.1, C47.1, C48.1, C50.1, J7.10, L1.2, R34.2, U7.1 (VIN), U7.3 (EN)
+24V: C1.1, C2.1, C3.1, C4.1, C9.1, C10.1, C11.1, C12.1, C16.1, C17.1, C18.1, C19.1, C23.1, C24.1, C25.1, C26.1, C43.2, C46.2, F1.2, J5.2, J6.2, J8.2, J9.2, J10.2, R38.1, U2.22 (VS), U2.28 (VS), U3.22 (VS), U3.28 (VS), U4.22 (VS), U4.28 (VS), U5.22 (VS), U5.28 (VS), U6.7 (VIN)
/BEEP: J7.1, U1.41 (PE10)
/BTN: J7.2, U1.42 (PE11)
/Buck enable: R37.1, R38.2, U1.1 (PE2), U6.2 (EN)
/D4: J7.5, U1.38 (PE7)
/D5: J7.6, U1.5 (PE6)
/D6: J7.7, U1.4 (PE5)
/D7: J7.8, U1.3 (PE4)
/D+: J14.A6 (D+), J14.B6 (D+), R41.2
/D-: J14.A7 (D-), J14.B7 (D-), R40.2
/Dir 1: U1.81 (PD0), U2.19 (DIR)
/Dir 2: U1.83 (PD2), U3.19 (DIR)
/Dir 3: U1.85 (PD4), U4.19 (DIR)
/Dir 4: U1.87 (PD6), U5.19 (DIR)
/ENCA: J17.3, U1.43 (PE12)
/ENCB: J17.5, U1.44 (PE13)
/Enable: U1.17 (PC2), U2.2 (~EN), U3.2 (~EN), U4.2 (~EN), U5.2 (~EN)
/Endstop1: J13.1, U1.61 (PD14)
/Endstop2: J13.3, U1.60 (PD13)
/Endstop3: J13.5, U1.59 (PD12)
/Endstop4: J13.7, U1.58 (PD11)
/Endstop5: J13.9, U1.57 (PD10)
/Endstop6: J13.11, U1.56 (PD9)
/LCD-CS: J7.4, U1.39 (PE8)
/LCD-EN: J7.3, U1.40 (PE9)
/MOS 1: R14.1, U1.35 (PB0)
/MOS 2: R15.1, U1.36 (PB1)
/MOS 4: R19.1, U1.92 (PB6)
/MOS 5: R21.1, U1.93 (PB7)
/MOS 6: R23.1, U1.95 (PB8)
/NRST: C40.1, J15.3, R33.2, SW1.1, U1.14 (NRST)
/RST: J17.8, U1.45 (PE14)
/RX 1: R3.2, U1.69 (PA10), U2.14 (~PD/UART)
/RX 2: R4.2, U1.26 (PA3), U3.14 (~PD/UART)
/RX 3: R7.2, U1.48 (PB11), U4.14 (~PD/UART)
/RX 4: R10.2, U1.24 (PA1), U5.14 (~PD/UART)
/SD-CS: J17.4, U1.51 (PB12)
/SD-DET: J17.7, U1.46 (PE15)
/SD-MISO: J17.1, U1.53 (PB14)
/SD-MOSI: J17.6, U1.54 (PB15)
/SD-SCK: J17.2, U1.52 (PB13)
/SWCLK: J15.2, U1.76 (PA14)
/SWDIO: J15.1, U1.72 (PA13)
/Step 1: U1.82 (PD1), U2.16 (STEP)
/Step 2: U1.84 (PD3), U3.16 (STEP)
/Step 3: U1.86 (PD5), U4.16 (STEP)
/Step 4: U1.88 (PD7), U5.16 (STEP)
/TX 1: R3.1, U1.68 (PA9)
/TX 2: R4.1, U1.25 (PA2)
/TX 3: R7.1, U1.47 (PB10)
/TX 4: R10.1, U1.23 (PA0)
/Thermistor 1: R26.2, U1.30 (PA5)
/Thermistor 2: R28.2, U1.32 (PA7)
/VDDA: C38.1, C39.1, FB1.2, U1.21 (VREF+), U1.22 (VDDA)
/Xin: C37.1, U1.12 (PH0), Y1.3
/Xout: R32.1, U1.13 (PH1)
/Z probe: J13.13, U1.55 (PD8)
GND: C2.2, C3.2, C4.2, C5.1, C6.1, C8.1, C9.2, C10.2, C11.2, C14.1, C15.1, C16.2, C17.2, C18.2, C21.1, C22.1, C23.2, C24.2, C25.2, C28.1, C29.2, C30.2, C31.2, C32.2, C33.2, C34.2, C35.2, C36.2, C37.2, C38.2, C39.2, C40.2, C42.2, C43.1, C45.2, C46.1, C47.2, C48.2, C49.2, C50.2, C51.1, C52.1, C53.1, D1.2 (A), J7.9, J11.1, J12.1, J13.2, J13.4, J13.6, J13.8, J13.10, J13.12, J13.14, J14.A1 (GND), J14.A12 (GND), J14.B1 (GND), J14.B12 (GND), J14.SH (SHIELD), J15.5, J16.1, J17.9, Q1.3 (S), Q2.3 (S), Q4.3 (S), Q5.3 (S), Q6.3 (S), R1.2, R2.2, R5.2, R6.2, R8.2, R9.2, R11.2, R12.2, R13.2, R16.2, R20.2, R22.2, R24.2, R29.2, R30.2, R31.1, R35.2, R36.2, R37.2, R39.2, SW1.2, U1.10 (VSS), U1.20 (VSSA), U1.27 (VSS), U1.74 (VSS), U1.99 (VSS), U2.3 (GND), U2.7 (SPREAD), U2.9 (MS1/AD0), U2.10 (MS2/AD1), U2.13 (CLK), U2.18 (GND), U2.25 (NC), U2.29 (GND), U3.3 (GND), U3.7 (SPREAD), U3.9 (MS1/AD0), U3.10 (MS2/AD1), U3.13 (CLK), U3.18 (GND), U3.25 (NC), U3.29 (GND), U4.3 (GND), U4.7 (SPREAD), U4.9 (MS1/AD0), U4.10 (MS2/AD1), U4.13 (CLK), U4.18 (GND), U4.25 (NC), U4.29 (GND), U5.3 (GND), U5.7 (SPREAD), U5.9 (MS1/AD0), U5.10 (MS2/AD1), U5.13 (CLK), U5.18 (GND), U5.25 (NC), U5.29 (GND), U6.5 (GND), U6.9 (GND), U7.2 (GND), Y1.2 (G), Y1.4 (G)
unnamed: C36.1, R32.2, Y1.1
unnamed: C44.2, R39.1
unnamed: C41.2, D1.1 (K), L1.1, U6.1 (SW)
unnamed: J1.1, U2.21 (OA2)
unnamed: J1.2, U2.24 (OA1)
unnamed: J1.3, U2.26 (OB1)
unnamed: J1.4, U2.1 (OB2)
unnamed: J2.1, U3.21 (OA2)
unnamed: J2.2, U3.24 (OA1)
unnamed: J2.3, U3.26 (OB1)
unnamed: J2.4, U3.1 (OB2)
unnamed: J3.1, U4.21 (OA2)
unnamed: J3.2, U4.24 (OA1)
unnamed: J3.3, U4.26 (OB1)
unnamed: J3.4, U4.1 (OB2)
unnamed: J4.1, U5.21 (OA2)
unnamed: J4.2, U5.24 (OA1)
unnamed: J4.3, U5.26 (OB1)
unnamed: J4.4, U5.1 (OB2)
unnamed: J5.1, Q1.2 (D)
unnamed: J6.1, Q2.2 (D)
unnamed: J8.1, Q4.2 (D)
unnamed: J9.1, Q5.2 (D)
unnamed: J10.1, Q6.2 (D)
unnamed: J11.2, R25.2, R26.1
unnamed: J12.2, R27.2, R28.1
unnamed: J14.A5 (CC1), R29.1
unnamed: J14.B5 (CC2), R30.1
unnamed: F1.1, J16.2
unnamed: Q1.1 (G), R13.1, R14.2
unnamed: Q2.1 (G), R15.2, R16.1
unnamed: Q4.1 (G), R19.2, R20.1
unnamed: Q5.1 (G), R21.2, R22.1
unnamed: Q6.1 (G), R23.2, R24.1
unnamed: R31.2, U1.94 (BOOT0)
unnamed: R40.1, U1.70 (PA11)
unnamed: R41.1, U1.71 (PA12)
unnamed: C52.2, U1.49 (VCAP_1)
unnamed: C53.2, U1.73 (VCAP_2)
unnamed: C6.2, U2.8 (5VOUT)
unnamed: R2.1, U2.23 (BRA)
unnamed: R1.1, U2.27 (BRB)
unnamed: C7.2, U2.5 (CPI)
unnamed: C7.1, U2.4 (CPO)
unnamed: C1.2, U2.6 (VCP)
unnamed: C14.2, U3.8 (5VOUT)
unnamed: R5.1, U3.23 (BRA)
unnamed: R6.1, U3.27 (BRB)
unnamed: C13.2, U3.5 (CPI)
unnamed: C13.1, U3.4 (CPO)
unnamed: C12.2, U3.6 (VCP)
unnamed: C21.2, U4.8 (5VOUT)
unnamed: R8.1, U4.23 (BRA)
unnamed: R9.1, U4.27 (BRB)
unnamed: C20.2, U4.5 (CPI)
unnamed: C20.1, U4.4 (CPO)
unnamed: C19.2, U4.6 (VCP)
unnamed: C28.2, U5.8 (5VOUT)
unnamed: R11.1, U5.23 (BRA)
unnamed: R12.1, U5.27 (BRB)
unnamed: C27.2, U5.5 (CPI)
unnamed: C27.1, U5.4 (CPO)
unnamed: C26.2, U5.6 (VCP)
unnamed: C41.1, U6.8 (BST)
unnamed: C44.1, C45.1, U6.3 (COMP)
unnamed: R34.1, R35.1, U6.4 (FB)
unnamed: R36.1, U6.6 (FREQ)

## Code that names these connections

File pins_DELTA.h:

/**
 * Marlin 3D Printer Firmware
 * Copyright (c) 2020 MarlinFirmware [https://github.com/MarlinFirmware/Marlin]
 *
 * Based on Sprinter and grbl.
 * Copyright (c) 2011 Camiel Gubbels / Erik van der Zalm
 *
 * This program is free software: you can redistribute it and/or modify
 * it under the terms of the GNU General Public License as published by
 * the Free Software Foundation, either version 3 of the License, or
 * (at your option) any later version.
 *
 * This program is distributed in the hope that it will be useful,
 * but WITHOUT ANY WARRANTY; without even the implied warranty of
 * MERCHANTABILITY or FITNESS FOR A PARTICULAR PURPOSE.  See the
 * GNU General Public License for more details.
 *
 * You should have received a copy of the GNU General Public License
 * along with this program.  If not, see <https://www.gnu.org/licenses/>.
 *
 */
#pragma once

#include "env_validate.h"


#define BOARD_INFO_NAME "DELTA"

//
// Modified from pins file for: BigTreeTech BTT002 v1.0 (STM32F407VG)
//


//
// Limit Switches
//
#define X_STOP_PIN                          PD14
#define Y_STOP_PIN                          PD13
#define Z_STOP_PIN                          PD12  

//
// Z Probe must be this pin
//
#ifndef Z_MIN_PROBE_PIN
  #define Z_MIN_PROBE_PIN                   PD8
#endif



// 
// Steppers
//
#define X_STEP_PIN                          PD1
#define X_DIR_PIN                           PD0
#define X_ENABLE_PIN                        -1
#ifndef X_CS_PIN
  #define X_CS_PIN                          -1
#endif

#define Y_STEP_PIN                          PD3
#define Y_DIR_PIN                           PD2
#define Y_ENABLE_PIN                        -1
 #ifndef Y_CS_PIN
  #define Y_CS_PIN                          -1
#endif

#define Z_STEP_PIN                          PD5
#define Z_DIR_PIN                           PD4
#define Z_ENABLE_PIN                        -1
#ifndef Z_CS_PIN
  #define Z_CS_PIN                          -1
#endif

#define E0_STEP_PIN                         PD7
#define E0_DIR_PIN                          PD6
#define E0_ENABLE_PIN                       -1
#ifndef E0_CS_PIN
  #define E0_CS_PIN                         -1
#endif

//
// SPI pins for TMC2130 stepper drivers
//
#ifndef TMC_SPI_MOSI
  #define TMC_SPI_MOSI                      PB15
#endif
#ifndef TMC_SPI_MISO
  #define TMC_SPI_MISO                      PB14
#endif
#ifndef TMC_SPI_SCK
  #define TMC_SPI_SCK                       PB13
#endif

#if HAS_TMC_UART
  /**
   * TMC2208/TMC2209 stepper drivers
   *
   * Hardware serial communication ports.
   * If undefined software serial is used according to the pins below
   */
  //#define X_HARDWARE_SERIAL Serial1
  //#define X2_HARDWARE_SERIAL Serial1
  //#define Y_HARDWARE_SERIAL  Serial1
  //#define Y2_HARDWARE_SERIAL Serial1
  //#define Z_HARDWARE_SERIAL  Serial1
  //#define Z2_HARDWARE_SERIAL Serial1
  //#define E0_HARDWARE_SERIAL Serial1
  //#define E1_HARDWARE_SERIAL Serial1
  //#define E2_HARDWARE_SERIAL Serial1
  //#define E3_HARDWARE_SERIAL Serial1
  //#define E4_HARDWARE_SERIAL Serial1

  #define X_SERIAL_TX_PIN                   PA9
  #define Y_SERIAL_TX_PIN                   PA2
  #define Z_SERIAL_TX_PIN                   PB10
  #define E0_SERIAL_TX_PIN                  PA0

  // Reduce baud rate to improve software serial reliability
  #ifndef TMC_BAUD_RATE
    #define TMC_BAUD_RATE                  19200
  #endif

#endif // HAS_TMC_UART

//
// Temperature Sensors
//
#define TEMP_0_PIN                          PA5   // T0 <-> E0
#define TEMP_BED_PIN                        PA7   // T2 <-> Bed



//
// Heaters / Fans
//
#define HEATER_0_PIN                        PB0   // Heater0
#define HEATER_BED_PIN                      PB1   // Hotbed


#define FAN0_PIN                        PB6   // Fan0
 
#define FAN1_PIN                        PB7   // Fan1

#define FAN2_PIN                        PB8   // Fan2


/**
 *                ------                                    ------
 * (BEEPER) PE10 | 1  2 | PE11  (BTN_ENC)     (MISO)   PB14 | 1  2 | PB13 (SCK)
 * (LCD_EN) PE9  | 3  4 | PE8  (LCD_RS)      (BTN_EN1) PE12 | 3  4 | PB12 (SD_SS)
 * (LCD_D4) PE7  | 5  6 | PE6 (LCD_D5)       (BTN_EN2) PE13 | 5  6 | PB15 (MOSI)
 * (LCD_D6) PE5  | 7  8 | PE4 (LCD_D7)       (SD_DET)  PE15 | 7  8 | RESET PE14
 *           GND | 9 10 | 5V                            GND | 9 10 | NC
 *                ------                                    ------
 *                 EXP1                                      EXP2
 */
#define EXP1_01_PIN                         PE10
#define EXP1_02_PIN                         PE11
#define EXP1_03_PIN                         PE9
#define EXP1_04_PIN                         PE8
#define EXP1_05_PIN                         PE7
#define EXP1_06_PIN                         PE6
#define EXP1_07_PIN                         PE5
#define EXP1_08_PIN                         PE4

#define EXP2_01_PIN                         PB14
#define EXP2_02_PIN                         PB13
#define EXP2_03_PIN                         PE12
#define EXP2_04_PIN                         PB12
#define EXP2_05_PIN                         PE13
#define EXP2_06_PIN                         PB15
#define EXP2_07_PIN                         PE15
#define EXP2_08_PIN                         -1
#define EXP2_10_PIN                         -1

// HAL SPI1 pins
#define SD_SCK_PIN                   EXP2_02_PIN  // SPI1 SCLK
#define SD_SS_PIN                    EXP2_04_PIN  // SPI1 SSEL
#define SD_MISO_PIN                  EXP2_01_PIN  // SPI1 MISO
#define SD_MOSI_PIN                  EXP2_06_PIN  // SPI1 MOSI

#define SDSS                         EXP2_04_PIN

//
// LCD / Controller - MINI12864 V2.0
//

#if HAS_WIRED_LCD
  #define BEEPER_PIN                 EXP1_01_PIN
  #define BTN_ENC                    EXP1_02_PIN

  #define SD_DETECT_PIN              EXP2_07_PIN

  #if ENABLED(CR10_STOCKDISPLAY)
    #define LCD_PINS_RS              EXP1_07_PIN

    #define BTN_EN1                  EXP1_03_PIN
    #define BTN_EN2                  EXP1_05_PIN

    #define LCD_PINS_EN              EXP1_08_PIN
    #define LCD_PINS_D4              EXP1_06_PIN

  #elif ENABLED(MKS_MINI_12864)

    #define DOGLCD_A0                EXP1_07_PIN
    #define DOGLCD_CS                EXP1_06_PIN
    #define BTN_EN1                  EXP2_03_PIN
    #define BTN_EN2                  EXP2_05_PIN

  #else

    #define LCD_PINS_RS              EXP1_04_PIN

    #define BTN_EN1                  EXP2_03_PIN
    #define BTN_EN2                  EXP2_05_PIN

    #define LCD_PINS_EN              EXP1_03_PIN
    #define LCD_PINS_D4              EXP1_05_PIN

    #if ENABLED(FYSETC_MINI_12864)
      #define DOGLCD_CS              EXP1_03_PIN
      #define DOGLCD_A0              EXP1_04_PIN
      #define DOGLCD_MOSI            EXP2_06_PIN
      #define DOGLCD_MISO            EXP2_01_PIN
      #define DOGLCD_SCK             EXP2_02_PIN

      #define LCD_BACKLIGHT_PIN             -1

      #define FORCE_SOFT_SPI

      #define LCD_RESET_PIN          EXP1_05_PIN  // Must be high or open for LCD to operate normally.

      #if ANY(FYSETC_MINI_12864_1_2, FYSETC_MINI_12864_2_0)
        #ifndef RGB_LED_R_PIN
          #define RGB_LED_R_PIN      EXP1_06_PIN
        #endif
        #ifndef RGB_LED_G_PIN
          #define RGB_LED_G_PIN      EXP1_07_PIN
        #endif
        #ifndef RGB_LED_B_PIN
          #define RGB_LED_B_PIN      EXP1_08_PIN
        #endif
      #elif ENABLED(FYSETC_MINI_12864_2_1)
        #define NEOPIXEL_PIN         EXP1_06_PIN
      #endif
    #endif // !FYSETC_MINI_12864

  #endif

  // Alter timing for graphical display
  #if IS_U8GLIB_ST7920
    #define BOARD_ST7920_DELAY_1              96
    #define BOARD_ST7920_DELAY_2              48
    #define BOARD_ST7920_DELAY_3             600
  #endif

#endif // HAS_WIRED_LCD

//

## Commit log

2026-06-05 Rename Gerber files.zip to PCB/Gerber files.zip
2026-06-05 Rename Delta 3d printer.kicad_pcb to PCB/Delta 3d printer.kicad_pcb
2026-06-05 Rename Delta 3d printer.kicad_pro to PCB/Delta 3d printer.kicad_pro
2026-06-05 Rename Delta 3d printer.kicad_sch to PCB/Delta 3d printer.kicad_sch
2026-06-05 Rename Marlin-2.1.2.7.zip to Firmware/Marlin-2.1.2.7.zip
2026-06-05 Rename Configuration.h to Firmware/Configuration.h
2026-06-05 Rename Configuration_adv.h to Firmware/Configuration_adv.h
2026-06-05 Rename pins_DELTA.h to Firmware/pins_DELTA.h
2026-06-05 Rename Base cover LCD_.step to CAD/Base cover LCD_.step
2026-06-05 Rename Base cover.step to CAD/Base cover.step
2026-06-05 Rename Bed support.step to CAD/Bed support.step
2026-06-05 Rename Bottom cover.step to CAD/Bottom cover.step
2026-06-05 Rename Carriage.step to CAD/Carriage.step
2026-06-05 Rename Drive arm.step to CAD/Drive arm.step
2026-06-05 Rename Extruder.step to CAD/Extruder.step
2026-06-05 Rename LCD front cover.step to CAD/LCD front cover.step
2026-06-05 Rename Limit switch bracket.step to CAD/Limit switch bracket.step
2026-06-05 Rename New motor mount.step to CAD/New motor mount.step
2026-06-05 Rename New top bracket.step to CAD/Top bracket.step
2026-06-05 Rename New motor mount.step to Motor mount.step
2026-06-05 Rename PSU Compartment.step to CAD/PSU Compartment.step
2026-06-05 Rename PSU base cover.step to CAD/PSU base cover.step
2026-06-05 Rename bottom bracket.step to CAD/Bottom bracket.step
2026-06-05 Rename New+assembly (1).stp to Assembly/Assembly.stp
2026-06-06 Rename Delta printer BOM - Sheet1.csv to Delta printer BOM.csv
2026-06-06 Rename Delta printer BOM.csv to BOM.csv
2026-06-07 Rename Delta printer BOM - Sheet1.csv to BOM.csv
2026-06-09 Rename New+assembly (2).stp to Assembly.stp
